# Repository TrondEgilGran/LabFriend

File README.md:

# LabFriend
Open Source USB Oscilloscope

Complete Open-Source USB basted oscillosope and measurement system.
2 Analog 200Msps channels 8 bit.
8 Digital 200Msps channels.
8 Digital Outputs
2 97KHz Audio frequency channel IO 24 bit.
3 High accuracy 16 bit DC inputs
1 8 bit 3Msps (low accuracy DAC).
1 DC output 0-5V max 20mA.

C-library for accessing HW. 
QT GUI Application.

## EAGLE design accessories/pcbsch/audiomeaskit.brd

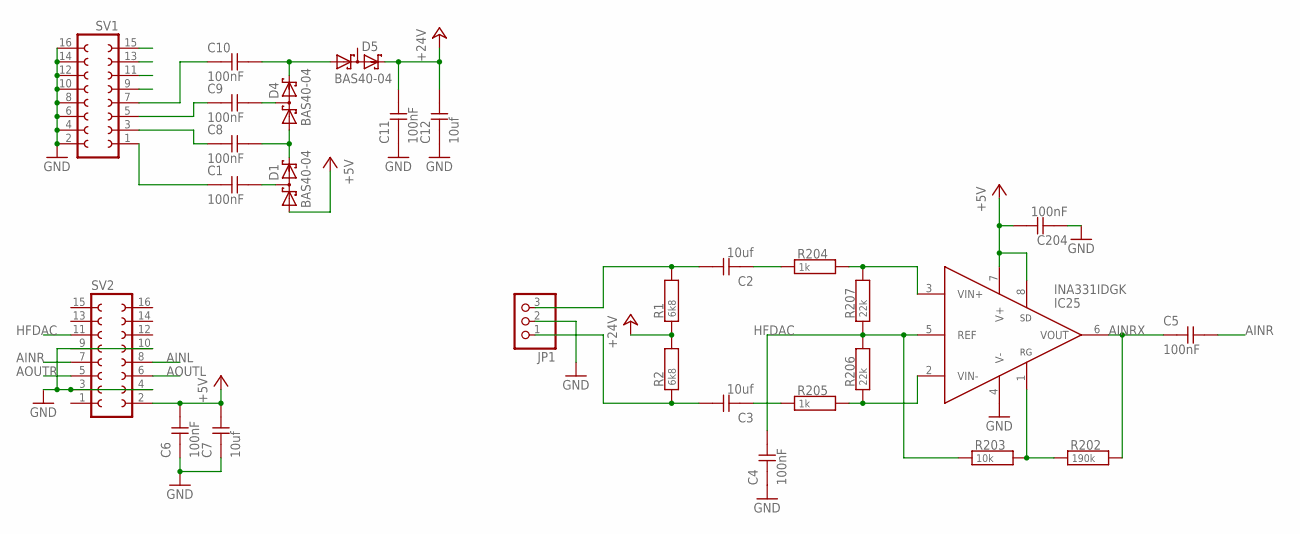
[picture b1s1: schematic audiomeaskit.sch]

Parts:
C1, C4, C5, C6, C8, C9, C10, C11: 100nF; 0603
C2, C3, C7, C12: 10uf; 0805
C204: 100nF; 0402
D1, D4, D5: BAS40-04; SOT23
IC25: INA331IDGK; MSOP08
JP1: PINHD-1X3; 1X03
R1, R2: 6k8; 0603
R202: 190k; 0603
R203: 10k; 0603
R204, R205: 1k; 0603
R206, R207: 22k; 0603
SV1, SV2: FE08-2

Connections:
+5V: C6.2, C7.2, C204.2, D1.1 (A1), IC25.7 (V+), IC25.8 (SD), SV2.2
+24V: C11.2, C12.2, D5.2 (C2), R1.1, R2.2
AINL: SV2.8
AINR: C5.2, SV2.7
AINRX: C5.1, IC25.6 (VOUT), R202.2
AOUTL: SV2.6
AOUTR: SV2.5
GND: C4.1, C6.1, C7.1, C11.1, C12.1, C204.1, IC25.4 (V-), JP1.2, SV1.2, SV1.4, SV1.6, SV1.8, SV1.10, SV1.12, SV1.14, SV1.16, SV2.3, SV2.4, SV2.9, SV2.10
HFDAC: C4.2, IC25.5 (REF), R203.1, R206.2, R207.1, SV2.11
unnamed: C8.1, SV1.3
unnamed: C3.2, JP1.1, R2.1
unnamed: C2.2, JP1.3, R1.2
unnamed: C1.1, SV1.1
unnamed: C1.2, D1.3 (C1A2)
unnamed: C10.1, SV1.7
unnamed: C8.2, D1.2 (C2), D4.1 (A1)
unnamed: C9.1, SV1.5
unnamed: C9.2, D4.3 (C1A2)
unnamed: C10.2, D4.2 (C2), D5.1 (A1)
unnamed: IC25.1 (RG), R202.1, R203.2
unnamed: IC25.3 (VIN+), R204.2, R207.2
unnamed: IC25.2 (VIN-), R205.2, R206.1
unnamed: C2.1, R204.1
unnamed: C3.1, R205.1
S1: SV1.9
S2: SV1.11
S3: SV1.13
S4: SV1.15

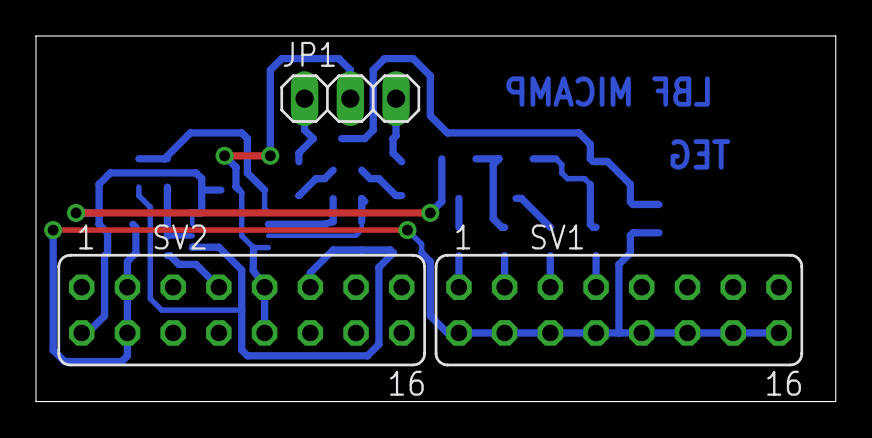
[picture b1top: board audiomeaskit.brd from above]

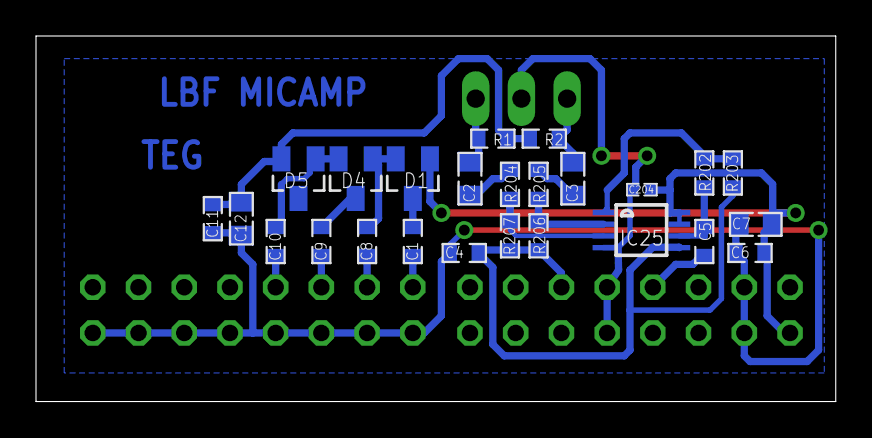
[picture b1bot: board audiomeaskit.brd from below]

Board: 2 copper layers, 44.4 x 20.3 mm, 28 parts (25 on the bottom side), 21 nets.

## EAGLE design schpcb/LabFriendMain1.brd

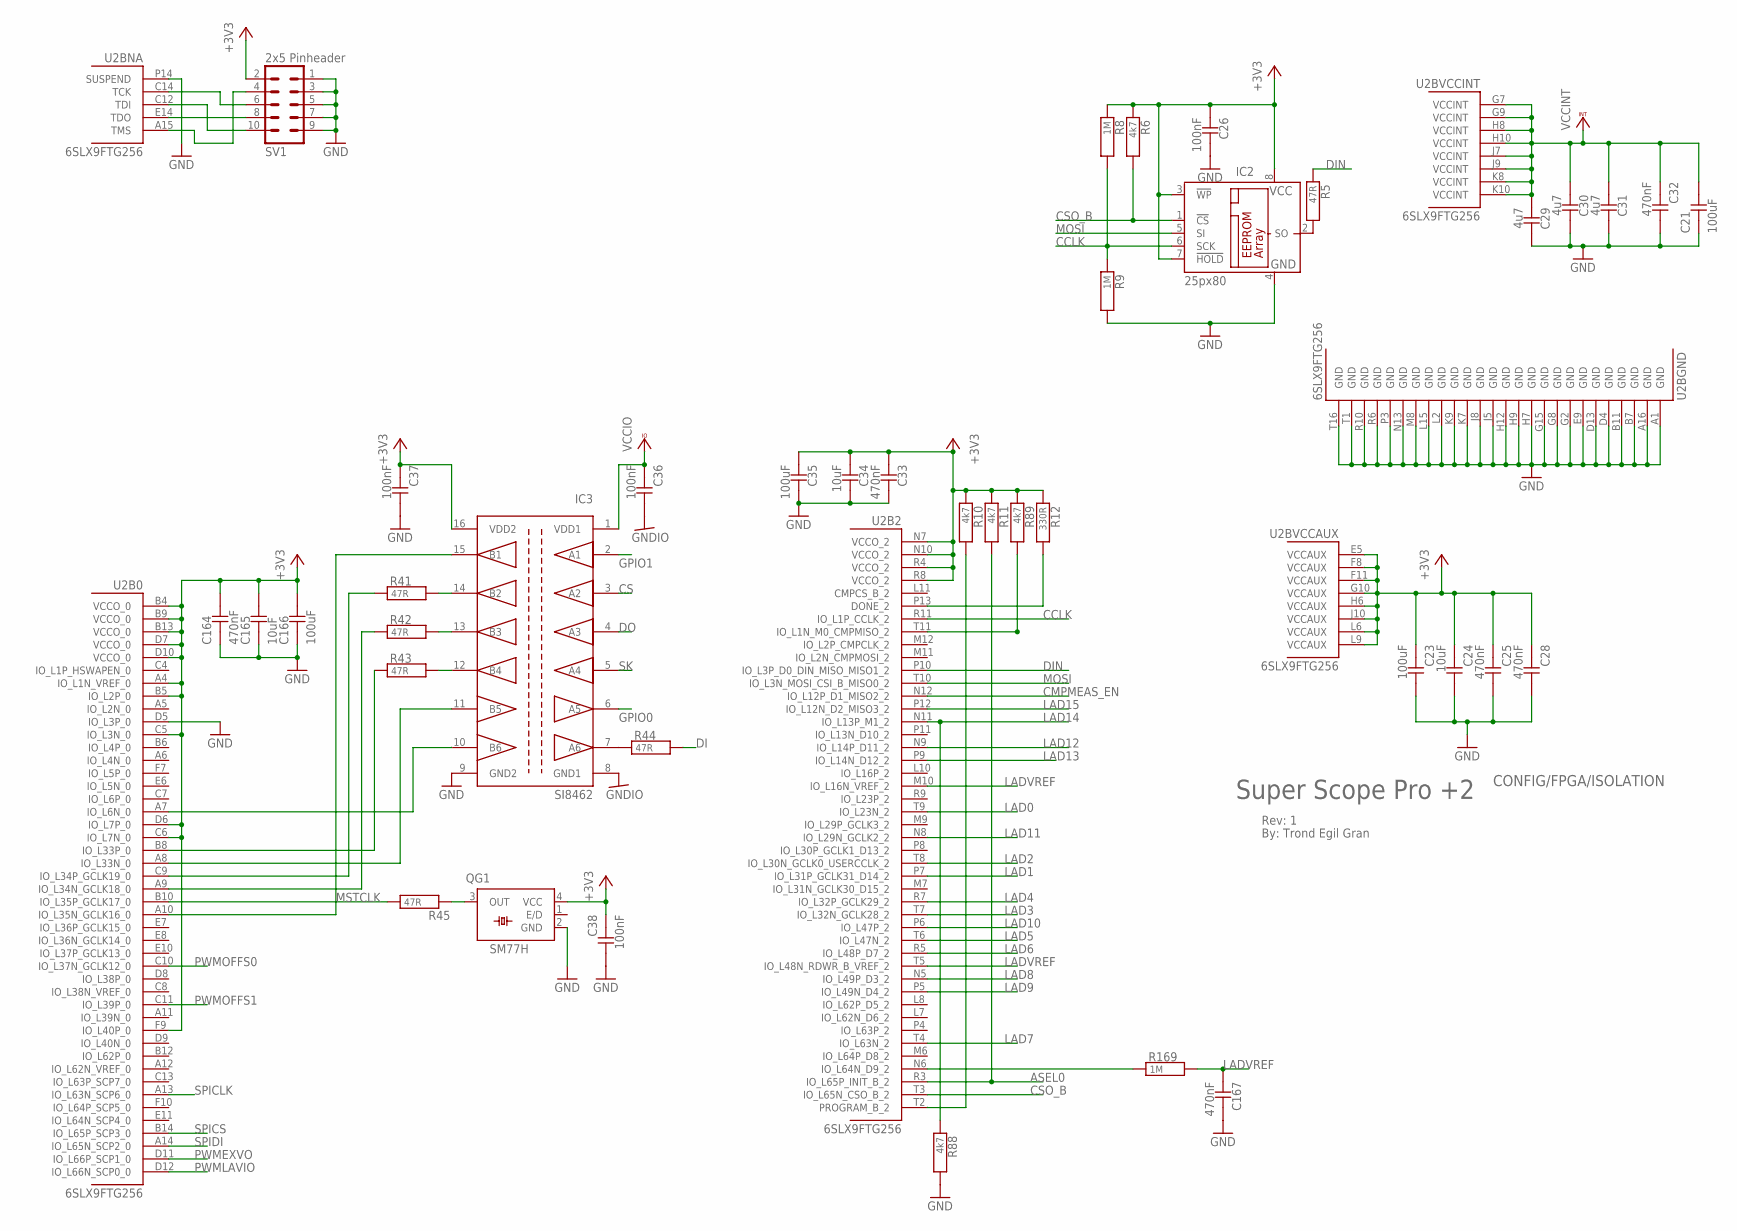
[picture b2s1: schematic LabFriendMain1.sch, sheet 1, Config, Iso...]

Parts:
C21, C23, C35, C166: 100uF; 1206
C24, C34, C165: 10uF; 0603
C25, C28, C32, C33, C164, C167: 470nF; 0402
C26, C36, C37, C38: 100nF; 0402
C29, C30, C31: 4u7; 0603
IC2: 25px80; SO-08
IC3: SI8462; SO16
QG1: SM77H
R5, R41, R42, R43, R44, R45: 47R; 0402
R6, R10, R11, R88, R89: 4k7; 0402
R8, R9, R169: 1M; 0402
R12: 330R; 0402
SV1: 2x5 Pinheader; ML10
U2: 6SLX9FTG256; FT256

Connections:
+3V3: C23.1, C24.1, C25.1, C26.1, C28.1, C33.1, C34.1, C35.1, C37.1, C38.1, C164.2, C165.2, C166.2, IC2.3 (!WP), IC2.7 (!HOLD), IC2.8 (VCC), IC3.16 (VDD2), QG1.4 (VCC), R6.1, R8.1, R10.1, R11.1, R12.1, R89.1, SV1.2, U2.A4 (IO_L1N_VREF_0), U2.B4 (VCCO_0), U2.B5 (IO_L2P_0), U2.B9 (VCCO_0), U2.B13 (VCCO_0), U2.C5 (IO_L3N_0), U2.C6 (IO_L7N_0), U2.D6 (IO_L7P_0), U2.D7 (VCCO_0), U2.D10 (VCCO_0), U2.E5 (VCCAUX), U2.F8 (VCCAUX), U2.F9 (IO_L40P_0), U2.F11 (VCCAUX), U2.G10 (VCCAUX), U2.H6 (VCCAUX), U2.J10 (VCCAUX), U2.L6 (VCCAUX), U2.L9 (VCCAUX), U2.N7 (VCCO_2), U2.N10 (VCCO_2), U2.R4 (VCCO_2), U2.R8 (VCCO_2); also elsewhere on the board
ASEL0: R11.2, U2.R3 (IO_L65P_INIT_B_2)
CCLK: IC2.6 (SCK), R8.2, R9.1, U2.R11 (IO_L1P_CCLK_2)
CMPMEAS_EN: U2.N12 (IO_L12P_D1_MISO2_2); also elsewhere on the board
CS: IC3.3 (A2); also elsewhere on the board
CSO_B: IC2.1 (!CS), R6.2, U2.T3 (IO_L65N_CSO_B_2)
DI: R44.2; also elsewhere on the board
DIN: R5.1, U2.P10 (IO_L3P_D0_DIN_MISO_MISO1_2)
DO: IC3.4 (A3); also elsewhere on the board
GND: C21.1, C23.2, C24.2, C25.2, C26.2, C28.2, C29.2, C30.2, C31.2, C32.2, C33.2, C34.2, C35.2, C37.2, C38.2, C164.1, C165.1, C166.1, C167.2, IC2.4 (GND), IC3.9 (GND2), QG1.2 (GND), R9.2, R88.2, SV1.1, SV1.3, SV1.5, SV1.7, SV1.9, U2.A1 (GND), U2.A16 (GND), U2.B7 (GND), U2.B11 (GND), U2.D4 (GND), U2.D5 (IO_L3P_0), U2.D13 (GND), U2.E9 (GND), U2.G2 (GND), U2.G8 (GND), U2.G15 (GND), U2.H7 (GND), U2.H9 (GND), U2.H12 (GND), U2.J5 (GND), U2.J8 (GND), U2.K7 (GND), U2.K9 (GND), U2.L2 (GND), U2.L15 (GND), U2.M8 (GND), U2.N13 (GND), U2.P3 (GND), U2.P14 (SUSPEND), U2.R6 (GND), U2.R10 (GND), U2.T1 (GND), U2.T16 (GND); also elsewhere on the board
GNDIO: C36.2, IC3.8 (GND1); also elsewhere on the board
GPIO0: IC3.6 (A5); also elsewhere on the board
GPIO1: IC3.2 (A1); also elsewhere on the board
LAD0: U2.T9 (IO_L23N_2); also elsewhere on the board
LAD1: U2.P7 (IO_L31P_GCLK31_D14_2); also elsewhere on the board
LAD2: U2.T8 (IO_L30N_GCLK0_USERCCLK_2); also elsewhere on the board
LAD3: U2.T7 (IO_L32N_GCLK28_2); also elsewhere on the board
LAD4: U2.R7 (IO_L32P_GCLK29_2); also elsewhere on the board
LAD5: U2.T6 (IO_L47N_2); also elsewhere on the board
LAD6: U2.R5 (IO_L48P_D7_2); also elsewhere on the board
LAD7: U2.T4 (IO_L63N_2); also elsewhere on the board
LAD8: U2.N5 (IO_L49P_D3_2); also elsewhere on the board
LAD9: U2.P5 (IO_L49N_D4_2); also elsewhere on the board
LAD10: U2.P6 (IO_L47P_2); also elsewhere on the board
LAD11: U2.N8 (IO_L29N_GCLK2_2); also elsewhere on the board
LAD12: U2.N9 (IO_L14P_D11_2); also elsewhere on the board
LAD13: U2.P9 (IO_L14N_D12_2); also elsewhere on the board
LAD14: R88.1, U2.N11 (IO_L13P_M1_2); also elsewhere on the board
LAD15: U2.P12 (IO_L12N_D2_MISO3_2); also elsewhere on the board
LADVREF: C167.1, R169.2, U2.M10 (IO_L16N_VREF_2), U2.T5 (IO_L48N_RDWR_B_VREF_2)
MOSI: IC2.5 (SI), U2.T10 (IO_L3N_MOSI_CSI_B_MISO0_2)
MSTCLK: R45.1, U2.B10 (IO_L35P_GCLK17_0)
unnamed: IC3.14 (B2), R41.2
unnamed: IC2.2 (SO), R5.2
unnamed: R10.2, U2.T2 (PROGRAM_B_2)
unnamed: R12.2, U2.P13 (DONE_2)
unnamed: IC3.15 (B1), U2.A10 (IO_L35N_GCLK16_0)
unnamed: SV1.4, U2.A15 (TMS)
unnamed: SV1.6, U2.C14 (TCK)
unnamed: SV1.8, U2.E14 (TDO)
unnamed: SV1.10, U2.C12 (TDI)
unnamed: R41.1, U2.C9 (IO_L34P_GCLK19_0)
unnamed: R42.1, U2.A9 (IO_L34N_GCLK18_0)
unnamed: IC3.10 (B6), U2.A7 (IO_L6N_0)
unnamed: IC3.13 (B3), R42.2
unnamed: IC3.12 (B4), R43.2
unnamed: IC3.7 (A6), R44.1
unnamed: QG1.3 (OUT), R45.2
unnamed: IC3.11 (B5), U2.A8 (IO_L33N_0)
unnamed: R43.1, U2.B8 (IO_L33P_0)
unnamed: R169.1, U2.N6 (IO_L64N_D9_2)
PULLUP1XA: R89.2, U2.T11 (IO_L1N_M0_CMPMISO_2)
PWMEXVO: U2.D11 (IO_L66P_SCP1_0); also elsewhere on the board
PWMLAVIO: U2.D12 (IO_L66N_SCP0_0); also elsewhere on the board
PWMOFFS0: U2.C10 (IO_L37N_GCLK12_0); also elsewhere on the board
PWMOFFS1: U2.C11 (IO_L39P_0); also elsewhere on the board
SK: IC3.5 (A4); also elsewhere on the board
SPICLK: U2.A13 (IO_L63N_SCP6_0); also elsewhere on the board
SPICS: U2.B14 (IO_L65P_SCP3_0); also elsewhere on the board
SPIDI: U2.A14 (IO_L65N_SCP2_0); also elsewhere on the board
VCCINT: C21.2, C29.1, C30.1, C31.1, C32.1, U2.G7 (VCCINT), U2.G9 (VCCINT), U2.H8 (VCCINT), U2.H10 (VCCINT), U2.J7 (VCCINT), U2.J9 (VCCINT), U2.K8 (VCCINT), U2.K10 (VCCINT); also elsewhere on the board
VCCIO: C36.1, IC3.1 (VDD1); also elsewhere on the board

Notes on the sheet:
Rev: 1
By: Trond Egil Gran
Super Scope Pro +2
CONFIG/FPGA/ISOLATION

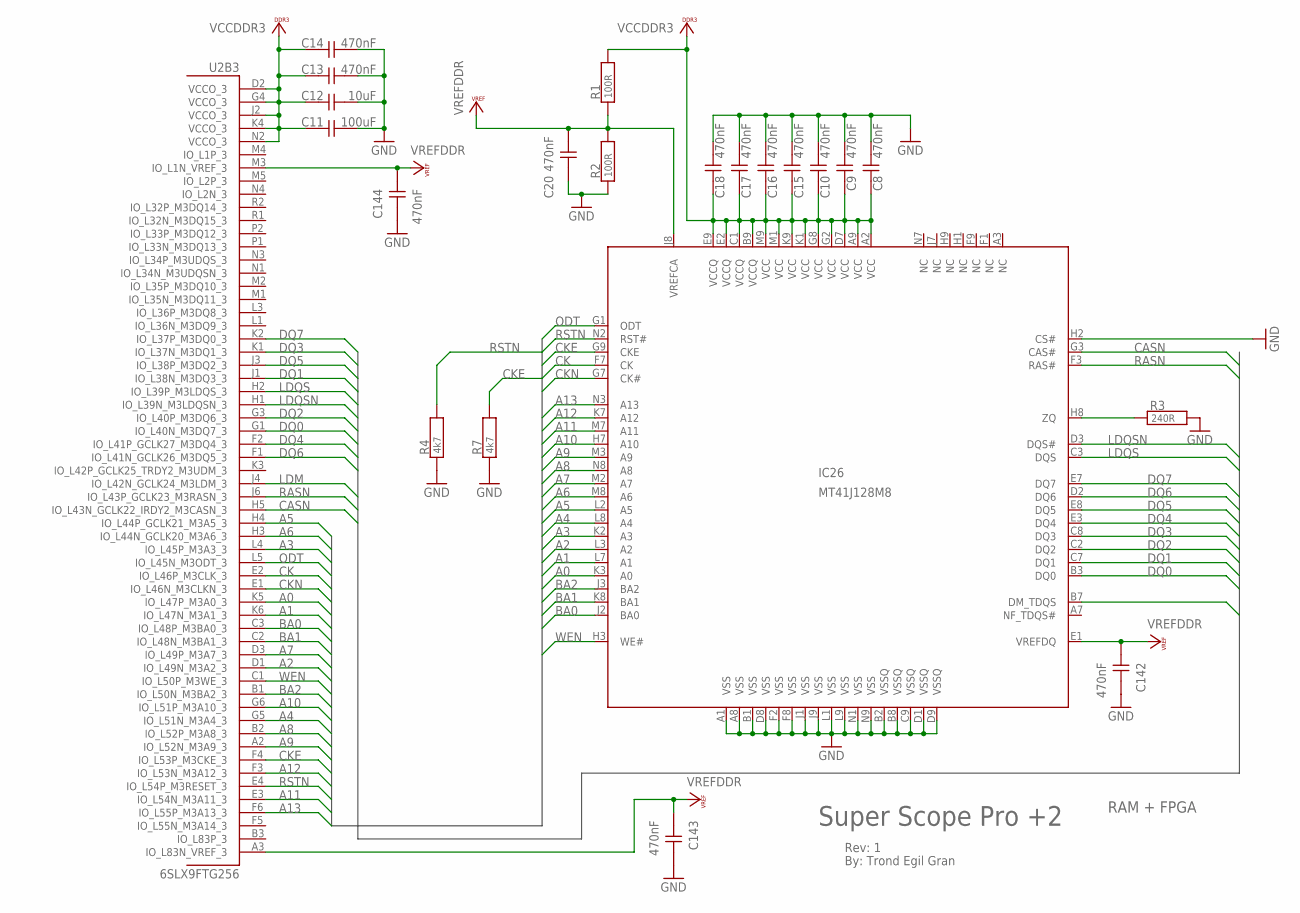
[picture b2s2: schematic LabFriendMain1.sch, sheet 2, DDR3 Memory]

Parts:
C8, C9, C10, C13, C14, C15, C16, C17, C18, C20, C142, C143, C144: 470nF; 0402
C11: 100uF; 1206
C12: 10uF; 0603
IC26: MT41J128M8; FBGA78
R1, R2: 100R; 0402
R3: 240R; 0603
R4, R7: 4k7; 0402
U2: 6SLX9FTG256; FT256

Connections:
A0: IC26.K3 (A0), U2.K5 (IO_L47P_M3A0_3)
A1: IC26.L7 (A1), U2.K6 (IO_L47N_M3A1_3)
A2: IC26.L3 (A2), U2.D1 (IO_L49N_M3A2_3)
A3: IC26.K2 (A3), U2.L4 (IO_L45P_M3A3_3)
A4: IC26.L8 (A4), U2.G5 (IO_L51N_M3A4_3)
A5: IC26.L2 (A5), U2.H4 (IO_L44P_GCLK21_M3A5_3)
A6: IC26.M8 (A6), U2.H3 (IO_L44N_GCLK20_M3A6_3)
A7: IC26.M2 (A7), U2.D3 (IO_L49P_M3A7_3)
A8: IC26.N8 (A8), U2.B2 (IO_L52P_M3A8_3)
A9: IC26.M3 (A9), U2.A2 (IO_L52N_M3A9_3)
A10: IC26.H7 (A10), U2.G6 (IO_L51P_M3A10_3)
A11: IC26.M7 (A11), U2.E3 (IO_L54N_M3A11_3)
A12: IC26.K7 (A12), U2.F3 (IO_L53N_M3A12_3)
A13: IC26.N3 (A13), U2.F6 (IO_L55P_M3A13_3)
BA0: IC26.J2 (BA0), U2.C3 (IO_L48P_M3BA0_3)
BA1: IC26.K8 (BA1), U2.C2 (IO_L48N_M3BA1_3)
BA2: IC26.J3 (BA2), U2.B1 (IO_L50N_M3BA2_3)
CASN: IC26.G3 (CAS#), U2.H5 (IO_L43N_GCLK22_IRDY2_M3CASN_3)
CK: IC26.F7 (CK), U2.E2 (IO_L46P_M3CLK_3)
CKE: IC26.G9 (CKE), R7.2, U2.F4 (IO_L53P_M3CKE_3)
CKN: IC26.G7 (CK#), U2.E1 (IO_L46N_M3CLKN_3)
DQ0: IC26.B3 (DQ0), U2.G1 (IO_L40N_M3DQ7_3)
DQ1: IC26.C7 (DQ1), U2.J1 (IO_L38N_M3DQ3_3)
DQ2: IC26.C2 (DQ2), U2.G3 (IO_L40P_M3DQ6_3)
DQ3: IC26.C8 (DQ3), U2.K1 (IO_L37N_M3DQ1_3)
DQ4: IC26.E3 (DQ4), U2.F2 (IO_L41P_GCLK27_M3DQ4_3)
DQ5: IC26.E8 (DQ5), U2.J3 (IO_L38P_M3DQ2_3)
DQ6: IC26.D2 (DQ6), U2.F1 (IO_L41N_GCLK26_M3DQ5_3)
DQ7: IC26.E7 (DQ7), U2.K2 (IO_L37P_M3DQ0_3)
GND: C8.2, C9.2, C10.2, C11.2, C12.2, C13.2, C14.2, C15.2, C16.2, C17.2, C18.2, C20.1, C142.1, C143.1, C144.1, IC26.A1 (VSS), IC26.A8 (VSS), IC26.B1 (VSS), IC26.B2 (VSSQ), IC26.B8 (VSSQ), IC26.C9 (VSSQ), IC26.D1 (VSSQ), IC26.D8 (VSS), IC26.D9 (VSSQ), IC26.F2 (VSS), IC26.F8 (VSS), IC26.H2 (CS#), IC26.J1 (VSS), IC26.J9 (VSS), IC26.L1 (VSS), IC26.L9 (VSS), IC26.N1 (VSS), IC26.N9 (VSS), R2.1, R3.2, R4.1, R7.1; also elsewhere on the board
LDM: IC26.B7 (DM_TDQS), U2.J4 (IO_L42N_GCLK24_M3LDM_3)
LDQS: IC26.C3 (DQS), U2.H2 (IO_L39P_M3LDQS_3)
LDQSN: IC26.D3 (DQS#), U2.H1 (IO_L39N_M3LDQSN_3)
unnamed: IC26.H8 (ZQ), R3.1
ODT: IC26.G1 (ODT), U2.L5 (IO_L45N_M3ODT_3)
RASN: IC26.F3 (RAS#), U2.J6 (IO_L43P_GCLK23_M3RASN_3)
RSTN: IC26.N2 (RST#), R4.2, U2.E4 (IO_L54P_M3RESET_3)
VCCDDR3: C8.1, C9.1, C10.1, C11.1, C12.1, C13.1, C14.1, C15.1, C16.1, C17.1, C18.1, IC26.A2 (VCC), IC26.A9 (VCC), IC26.B9 (VCCQ), IC26.C1 (VCCQ), IC26.D7 (VCC), IC26.E2 (VCCQ), IC26.E9 (VCCQ), IC26.G2 (VCC), IC26.G8 (VCC), IC26.K1 (VCC), IC26.K9 (VCC), IC26.M1 (VCC), IC26.M9 (VCC), R1.2, U2.D2 (VCCO_3), U2.G4 (VCCO_3), U2.J2 (VCCO_3), U2.K4 (VCCO_3), U2.N2 (VCCO_3); also elsewhere on the board
VREFDDR: C20.2, C142.2, C143.2, C144.2, IC26.E1 (VREFDQ), IC26.J8 (VREFCA), R1.1, R2.2, U2.A3 (IO_L83N_VREF_3), U2.M3 (IO_L1N_VREF_3)
WEN: IC26.H3 (WE#), U2.C1 (IO_L50P_M3WE_3)

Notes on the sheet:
Rev: 1
By: Trond Egil Gran
Super Scope Pro +2
RAM + FPGA

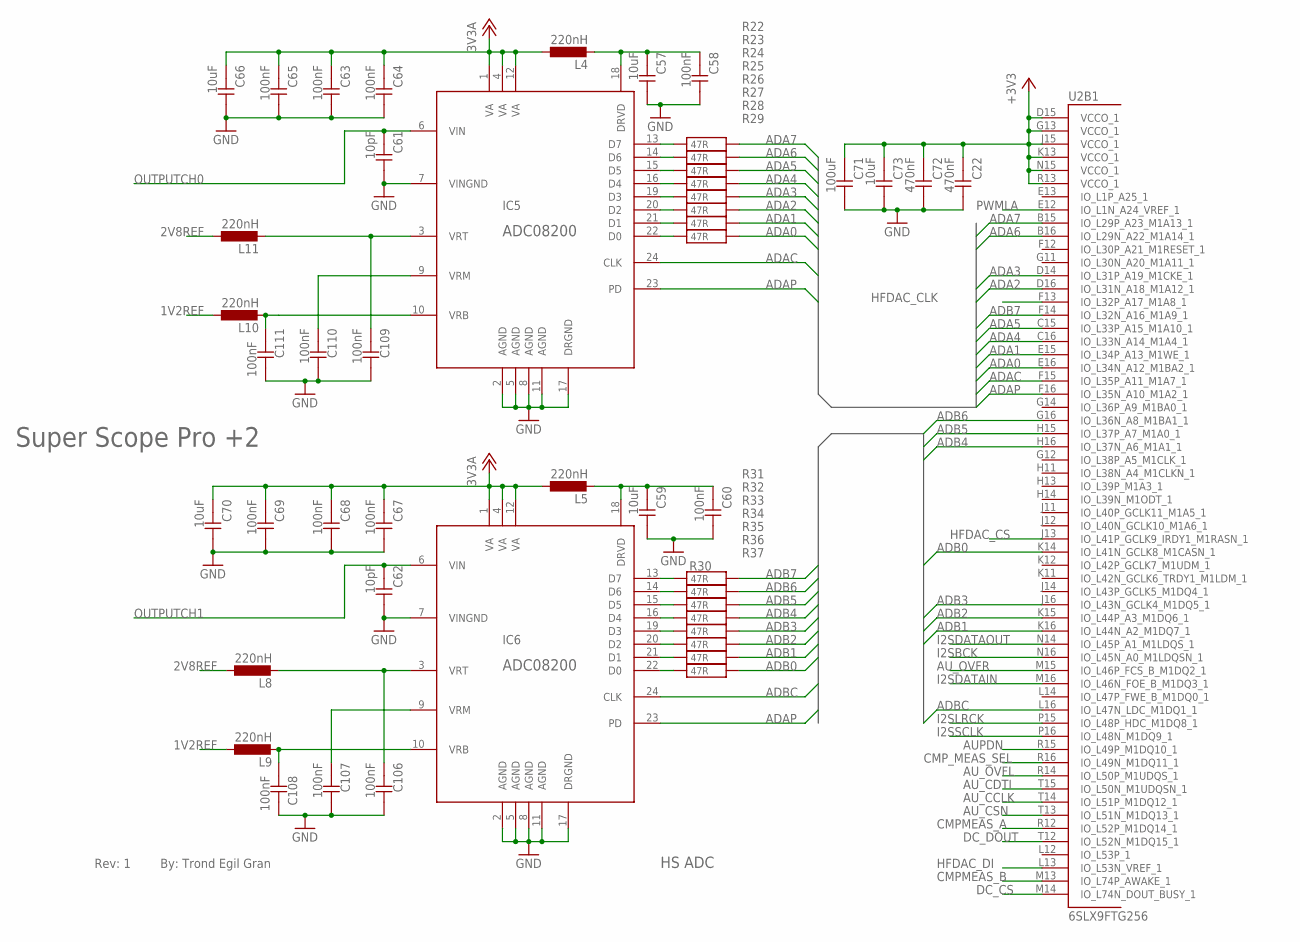
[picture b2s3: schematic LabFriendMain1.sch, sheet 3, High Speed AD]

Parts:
C22, C72: 470nF; 0402
C57, C59, C66, C70, C73: 10uF; 0603
C58, C60, C63, C64, C65, C67, C68, C69, C106, C107, C108, C109, C110, C111: 100nF; 0402
C61, C62: 10pF; 0402
C71: 100uF; 1206
IC5, IC6: ADC08200; TSSOP24
L4, L5, L8, L9, L10, L11: 220nH; 0603
R22, R23, R24, R25, R26, R27, R28, R29, R30, R31, R32, R33, R34, R35, R36, R37: 47R; 0402
U2: 6SLX9FTG256; FT256

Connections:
1V2REF: L9.1, L10.1; also elsewhere on the board
1V2REFAD0: C111.1, IC5.10 (VRB), L10.2
1V2REFAD1: C108.1, IC6.10 (VRB), L9.2
2V8REF: L8.1, L11.1; also elsewhere on the board
2V8REFAD0: C109.1, IC5.3 (VRT), L11.2
2V8REFAD1: C106.1, IC6.3 (VRT), L8.2
3V3A: C63.1, C64.1, C65.1, C66.1, C67.1, C68.1, C69.1, C70.1, IC5.1 (VA), IC5.4 (VA), IC5.12 (VA), IC6.1 (VA), IC6.4 (VA), IC6.12 (VA), L4.1, L5.1; also elsewhere on the board
+3V3: C22.1, C71.1, C72.1, C73.1, U2.D15 (VCCO_1), U2.G13 (VCCO_1), U2.J15 (VCCO_1), U2.K13 (VCCO_1), U2.N15 (VCCO_1), U2.R13 (VCCO_1); also elsewhere on the board
ADA0: R29.2, U2.E16 (IO_L34N_A12_M1BA2_1)
ADA1: R28.2, U2.E15 (IO_L34P_A13_M1WE_1)
ADA2: R27.2, U2.D16 (IO_L31N_A18_M1A12_1)
ADA3: R26.2, U2.D14 (IO_L31P_A19_M1CKE_1)
ADA4: R25.2, U2.C16 (IO_L33N_A14_M1A4_1)
ADA5: R24.2, U2.C15 (IO_L33P_A15_M1A10_1)
ADA6: R23.2, U2.B16 (IO_L29N_A22_M1A14_1)
ADA7: R22.2, U2.B15 (IO_L29P_A23_M1A13_1)
ADAC: IC5.24 (CLK), U2.F15 (IO_L35P_A11_M1A7_1)
ADAP: IC5.23 (PD), IC6.23 (PD), U2.F16 (IO_L35N_A10_M1A2_1)
ADB0: R37.2, U2.K14 (IO_L41N_GCLK8_M1CASN_1)
ADB1: R36.2, U2.K16 (IO_L44N_A2_M1DQ7_1)
ADB2: R35.2, U2.K15 (IO_L44P_A3_M1DQ6_1)
ADB3: R34.2, U2.J16 (IO_L43N_GCLK4_M1DQ5_1)
ADB4: R33.2, U2.H16 (IO_L37N_A6_M1A1_1)
ADB5: R32.2, U2.H15 (IO_L37P_A7_M1A0_1)
ADB6: R31.2, U2.G16 (IO_L36N_A8_M1BA1_1)
ADB7: R30.2, U2.F14 (IO_L32N_A16_M1A9_1)
ADBC: IC6.24 (CLK), U2.L16 (IO_L47N_LDC_M1DQ1_1)
AUPDN: U2.R15 (IO_L49P_M1DQ10_1); also elsewhere on the board
AU_CCLK: U2.T14 (IO_L51P_M1DQ12_1); also elsewhere on the board
AU_CDTI: U2.T15 (IO_L50N_M1UDQSN_1); also elsewhere on the board
AU_CSN: U2.T13 (IO_L51N_M1DQ13_1); also elsewhere on the board
AU_OVFL: U2.R14 (IO_L50P_M1UDQS_1); also elsewhere on the board
AU_OVFR: U2.M15 (IO_L46P_FCS_B_M1DQ2_1); also elsewhere on the board
CMPMEAS_A: U2.R12 (IO_L52P_M1DQ14_1); also elsewhere on the board
CMPMEAS_B: U2.M13 (IO_L74P_AWAKE_1); also elsewhere on the board
CMP_MEAS_SEL: U2.R16 (IO_L49N_M1DQ11_1); also elsewhere on the board
DC_CS: U2.M14 (IO_L74N_DOUT_BUSY_1); also elsewhere on the board
DC_DOUT: U2.T12 (IO_L52N_M1DQ15_1); also elsewhere on the board
GND: C22.2, C57.2, C58.2, C59.2, C60.2, C61.2, C62.2, C63.2, C64.2, C65.2, C66.2, C67.2, C68.2, C69.2, C70.2, C71.2, C72.2, C73.2, C106.2, C107.2, C108.2, C109.2, C110.2, C111.2, IC5.2 (AGND), IC5.5 (AGND), IC5.7 (VINGND), IC5.8 (AGND), IC5.11 (AGND), IC5.17 (DRGND), IC6.2 (AGND), IC6.5 (AGND), IC6.7 (VINGND), IC6.8 (AGND), IC6.11 (AGND), IC6.17 (DRGND); also elsewhere on the board
HFDAC_CLK: U2.F13 (IO_L32P_A17_M1A8_1); also elsewhere on the board
HFDAC_CS: U2.J13 (IO_L41P_GCLK9_IRDY1_M1RASN_1); also elsewhere on the board
HFDAC_DI: U2.L13 (IO_L53N_VREF_1); also elsewhere on the board
I2SBCK: U2.N16 (IO_L45N_A0_M1LDQSN_1); also elsewhere on the board
I2SDATAIN: U2.M16 (IO_L46N_FOE_B_M1DQ3_1); also elsewhere on the board
I2SDATAOUT: U2.N14 (IO_L45P_A1_M1LDQS_1); also elsewhere on the board
I2SLRCK: U2.P15 (IO_L48P_HDC_M1DQ8_1); also elsewhere on the board
I2SSCLK: U2.P16 (IO_L48N_M1DQ9_1); also elsewhere on the board
unnamed: C57.1, C58.1, IC5.18 (DRVD), L4.2
unnamed: IC5.13 (D7), R22.1
unnamed: C59.1, C60.1, IC6.18 (DRVD), L5.2
unnamed: IC5.14 (D6), R23.1
unnamed: IC5.15 (D5), R24.1
unnamed: IC5.16 (D4), R25.1
unnamed: IC5.19 (D3), R26.1
unnamed: IC5.20 (D2), R27.1
unnamed: IC5.21 (D1), R28.1
unnamed: IC5.22 (D0), R29.1
unnamed: IC6.13 (D7), R30.1
unnamed: IC6.14 (D6), R31.1
unnamed: IC6.15 (D5), R32.1
unnamed: IC6.16 (D4), R33.1
unnamed: IC6.19 (D3), R34.1
unnamed: IC6.20 (D2), R35.1
unnamed: IC6.21 (D1), R36.1
unnamed: IC6.22 (D0), R37.1
NONO1: C110.1, IC5.9 (VRM)
NONO2: C107.1, IC6.9 (VRM)
OUTPUTCH0: C61.1, IC5.6 (VIN); also elsewhere on the board
OUTPUTCH1: C62.1, IC6.6 (VIN); also elsewhere on the board
PWMLA: U2.E12 (IO_L1N_A24_VREF_1); also elsewhere on the board

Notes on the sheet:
Rev: 1
By: Trond Egil Gran
Super Scope Pro +2
HS ADC

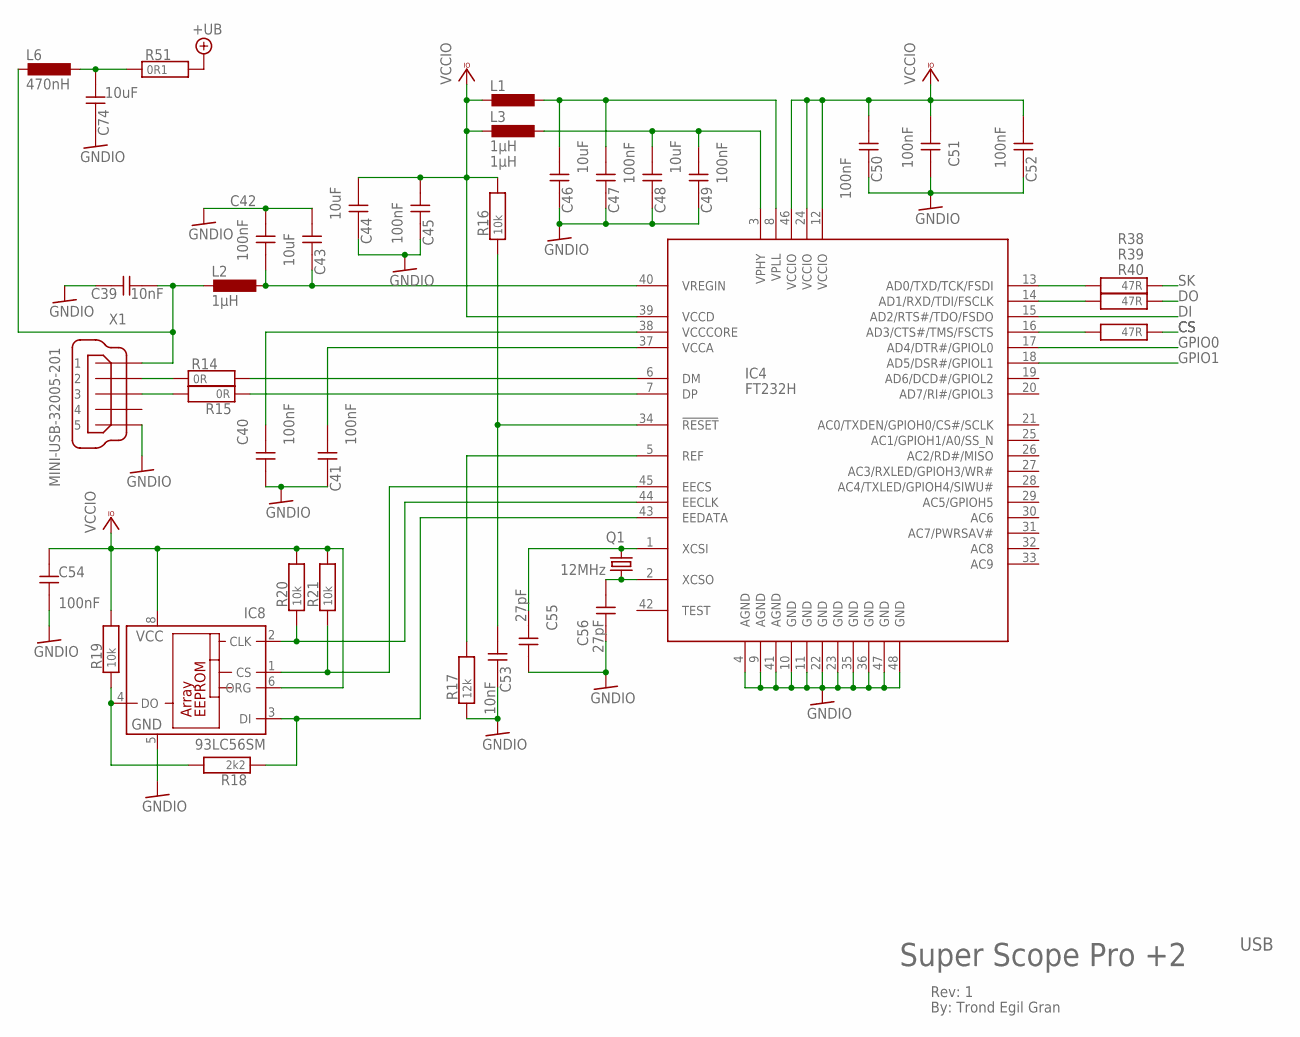
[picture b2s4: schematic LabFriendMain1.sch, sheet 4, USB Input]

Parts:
C39, C53: 10nF; 0402
C40, C41, C42, C45, C47, C49, C50, C51, C52, C54: 100nF; 0402
C43, C44, C46, C48, C74: 10uF; 0603
C55, C56: 27pF; 0603
IC4: FT232H; LQFP48
IC8: 93LC56SM; SO-08M
L1, L2, L3: 1µH; L3216C
L6: 470nH; L3216C
Q1: 12MHz; HC49UP
R14, R15: 0R; 0603
R16, R19, R20, R21: 10k; 0603
R17: 12k; 0603
R18: 2k2; 0402
R38, R39, R40: 47R; 0402
R51: 0R1; 0603
X1: MINI-USB-32005-201; 32005-201

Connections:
+UB: R51.2; also elsewhere on the board
CS: R40.1; also elsewhere on the board
DI: IC4.15 (AD2/RTS#/TDO/FSDO); also elsewhere on the board
DO: R39.1; also elsewhere on the board
GNDIO: C39.2, C40.2, C41.2, C42.1, C43.1, C44.2, C45.2, C46.2, C47.2, C48.2, C49.2, C50.2, C51.2, C52.2, C53.2, C54.2, C55.1, C56.1, C74.2, IC4.4 (AGND), IC4.9 (AGND), IC4.10 (GND), IC4.11 (GND), IC4.22 (GND), IC4.23 (GND), IC4.35 (GND), IC4.36 (GND), IC4.41 (AGND), IC4.47 (GND), IC4.48 (GND), IC8.5 (GND), R17.1, X1.5; also elsewhere on the board
GPIO0: IC4.17 (AD4/DTR#/GPIOL0); also elsewhere on the board
GPIO1: IC4.18 (AD5/DSR#/GPIOL1); also elsewhere on the board
unnamed: IC4.13 (AD0/TXD/TCK/FSDI), R38.2
unnamed: R14.1, X1.2
unnamed: C39.1, L2.2, L6.2, X1.1
unnamed: C42.2, C43.2, IC4.40 (VREGIN), L2.1
unnamed: IC4.6 (DM), R14.2
unnamed: IC4.7 (DP), R15.1
unnamed: R15.2, X1.3
unnamed: C41.1, IC4.37 (VCCA)
unnamed: C40.1, IC4.38 (VCCCORE)
unnamed: C53.1, IC4.34 (!RESET), R16.1
unnamed: C46.1, C47.1, IC4.8 (VPLL), L1.1
unnamed: C48.1, C49.1, IC4.3 (VPHY), L3.1
unnamed: IC4.5 (REF), R17.2
unnamed: IC8.4 (DO), R18.2, R19.1
unnamed: IC4.43 (EEDATA), IC8.3 (DI), R18.1
unnamed: C56.2, IC4.2 (XCSO), Q1.1
unnamed: IC4.44 (EECLK), IC8.2 (CLK), R20.1
unnamed: IC4.45 (EECS), IC8.1 (CS), R21.1
unnamed: C55.2, IC4.1 (XCSI), Q1.2
unnamed: IC4.14 (AD1/RXD/TDI/FSCLK), R39.2
unnamed: IC4.16 (AD3/CTS#/TMS/FSCTS), R40.2
unnamed: C74.1, L6.1, R51.1
SK: R38.1; also elsewhere on the board
VCCIO: C44.1, C45.1, C50.1, C51.1, C52.1, C54.1, IC4.12 (VCCIO), IC4.24 (VCCIO), IC4.39 (VCCD), IC4.46 (VCCIO), IC8.6 (ORG), IC8.8 (VCC), L1.2, L3.2, R16.2, R19.2, R20.2, R21.2; also elsewhere on the board

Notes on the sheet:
Rev: 1
By: Trond Egil Gran
Super Scope Pro +2
USB

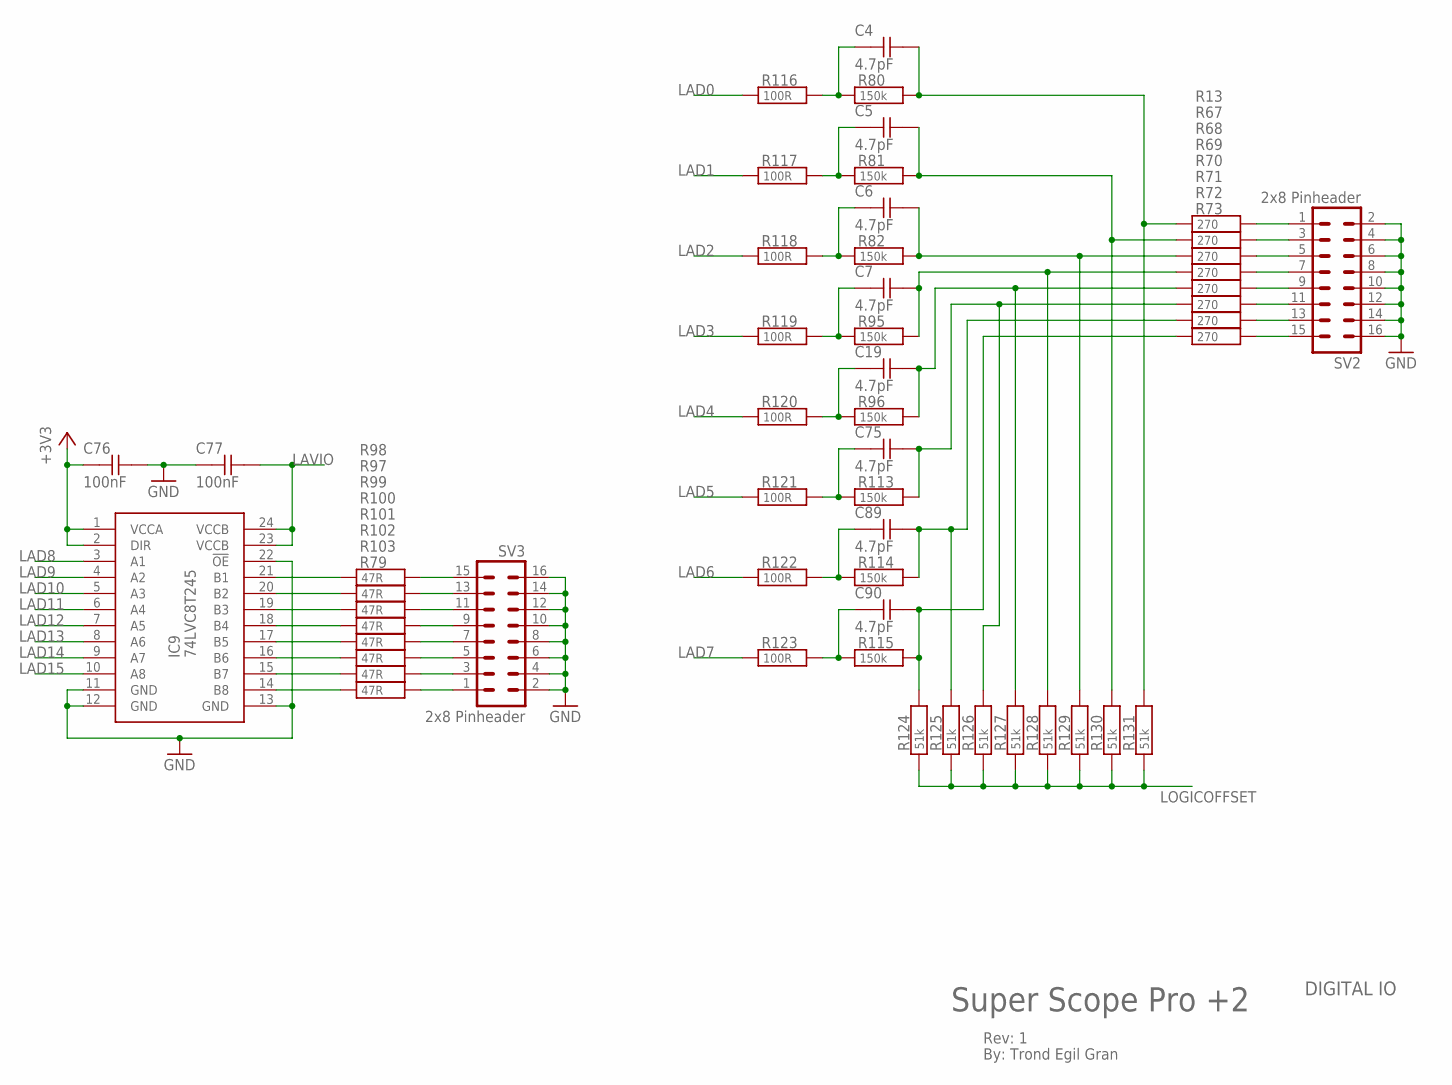
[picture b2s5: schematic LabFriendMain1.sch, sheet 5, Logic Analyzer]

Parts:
C4, C5, C6, C7, C19, C75, C89, C90: 4.7pF; 0402
C76, C77: 100nF; 0402
IC9: 74LVC8T245; R-PDSO-G24
R13, R67, R68, R69, R70, R71, R72, R73: 270; 0402
R79, R97, R98, R99, R100, R101, R102, R103: 47R; 0402
R80, R81, R82, R95, R96, R113, R114, R115: 150k; 0402
R116, R117, R118, R119, R120, R121, R122, R123: 100R; 0402
R124, R125, R126, R127, R128, R129, R130, R131: 51k; 0402
SV2, SV3: 2x8 Pinheader; MA08-2W

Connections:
+3V3: C76.1, IC9.1 (VCCA), IC9.2 (DIR); also elsewhere on the board
GND: C76.2, C77.1, IC9.11 (GND), IC9.12 (GND), IC9.13 (GND), IC9.22 (!OE), SV2.2, SV2.4, SV2.6, SV2.8, SV2.10, SV2.12, SV2.14, SV2.16, SV3.2, SV3.4, SV3.6, SV3.8, SV3.10, SV3.12, SV3.14, SV3.16; also elsewhere on the board
LAD0: R116.1; also elsewhere on the board
LAD1: R117.1; also elsewhere on the board
LAD2: R118.1; also elsewhere on the board
LAD3: R119.1; also elsewhere on the board
LAD4: R120.1; also elsewhere on the board
LAD5: R121.1; also elsewhere on the board
LAD6: R122.1; also elsewhere on the board
LAD7: R123.1; also elsewhere on the board
LAD8: IC9.3 (A1); also elsewhere on the board
LAD9: IC9.4 (A2); also elsewhere on the board
LAD10: IC9.5 (A3); also elsewhere on the board
LAD11: IC9.6 (A4); also elsewhere on the board
LAD12: IC9.7 (A5); also elsewhere on the board
LAD13: IC9.8 (A6); also elsewhere on the board
LAD14: IC9.9 (A7); also elsewhere on the board
LAD15: IC9.10 (A8); also elsewhere on the board
LAVIO: C77.2, IC9.23 (VCCB), IC9.24 (VCCB); also elsewhere on the board
LOGICOFFSET: R124.1, R125.1, R126.1, R127.1, R128.1, R129.1, R130.1, R131.1; also elsewhere on the board
unnamed: IC9.14 (B8), R79.1
unnamed: R13.2, SV2.1
unnamed: R67.2, SV2.3
unnamed: C4.2, R13.1, R80.2, R131.2
unnamed: C5.2, R67.1, R81.2, R130.2
unnamed: C6.2, R68.1, R82.2, R129.2
unnamed: C7.2, R69.1, R95.2, R128.2
unnamed: C19.2, R70.1, R96.2, R127.2
unnamed: C75.2, R71.1, R113.2, R126.2
unnamed: C89.2, R72.1, R114.2, R125.2
unnamed: C90.2, R73.1, R115.2, R124.2
unnamed: R68.2, SV2.5
unnamed: R69.2, SV2.7
unnamed: R97.2, SV3.15
unnamed: R70.2, SV2.9
unnamed: C4.1, R80.1, R116.2
unnamed: R71.2, SV2.11
unnamed: R72.2, SV2.13
unnamed: R73.2, SV2.15
unnamed: C5.1, R81.1, R117.2
unnamed: C6.1, R82.1, R118.2
unnamed: C7.1, R95.1, R119.2
unnamed: IC9.21 (B1), R97.1
unnamed: R98.2, SV3.13
unnamed: R99.2, SV3.11
unnamed: R100.2, SV3.9
unnamed: R101.2, SV3.7
unnamed: R102.2, SV3.5
unnamed: R103.2, SV3.3
unnamed: R79.2, SV3.1
unnamed: IC9.20 (B2), R98.1
unnamed: IC9.19 (B3), R99.1
unnamed: IC9.18 (B4), R100.1
unnamed: IC9.17 (B5), R101.1
unnamed: IC9.16 (B6), R102.1
unnamed: IC9.15 (B7), R103.1
unnamed: C19.1, R96.1, R120.2
unnamed: C75.1, R113.1, R121.2
unnamed: C89.1, R114.1, R122.2
unnamed: C90.1, R115.1, R123.2

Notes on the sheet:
Rev: 1
By: Trond Egil Gran
Super Scope Pro +2
DIGITAL IO
